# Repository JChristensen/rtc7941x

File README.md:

# MCP78411/12 RTC Break-Out Board with Temperature Sensor
https://github.com/JChristensen/rtc7941x  
README file  
Jack Christensen  
Apr-2014

## License
  
This work is licensed under the [Creative Commons Attribution-ShareAlike 4.0 International License](https://creativecommons.org/licenses/by-sa/4.0/).

## Introduction
Break-out board for the Microchip MCP78411/12 Real-Time Clock. Optionally, an MCP9800/02 temperature sensor can be installed on the board.

For an Arduino library that supports the MCP79412 RTC, see: https://github.com/JChristensen/MCP79412RTC

For an Arduino library that supports the MCP980x temperature sensor, see: https://github.com/JChristensen/MCP9800

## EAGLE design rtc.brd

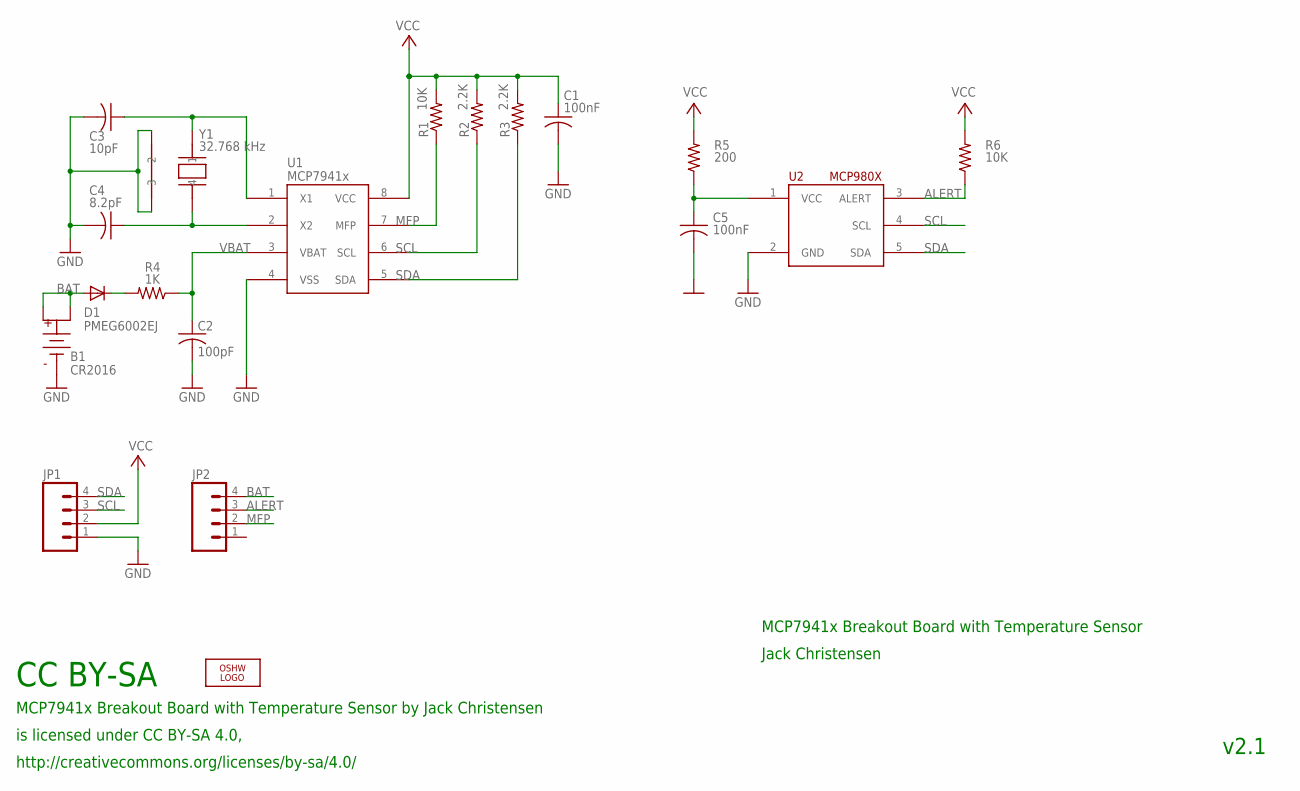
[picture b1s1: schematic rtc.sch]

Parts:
B1: CR2016; BAT-HLD-002-SMT
C1, C5: 100nF; M0805
C2: 100pF; M0805
C3: 10pF; M0805
C4: 8.2pF; M0805
D1: PMEG6002EJ; SOD-323F-A
JP1, JP2: M04LOCK; 1X04_LOCK
LOGO2: OSHW_LOGO_8MILX0150-NT; OSHW_8X150_NOTEXT
R1, R6: 10K; M0805
R2, R3: 2.2K; M0805
R4: 1K; M0805
R5: 200; M0805
U1: MCP7941x; MSOP8
U2: MCP980X; SOT23-5L
Y1: 32.768 kHz; CRYSTAL-CITIZEN-CM2XXC

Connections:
ALERT: JP2.3, R6.1, U2.3 (ALERT)
BAT: B1.POS1, B1.POS2, D1.A, JP2.4
GND: B1.NEG (B-), C1.2, C2.2, C3.2, C4.2, C5.2, JP1.1, U1.4 (VSS), U2.2 (GND), Y1.P$2 (2), Y1.P$3 (3)
MFP: JP2.2, R1.1, U1.7 (MFP)
unnamed: D1.K, R4.2
unnamed: C4.1, U1.2 (X2), Y1.P$4 (4)
unnamed: C3.1, U1.1 (X1), Y1.P$1 (1)
unnamed: C5.1, R5.1, U2.1 (VCC)
SCL: JP1.3, R2.1, U1.6 (SCL), U2.4 (SCL)
SDA: JP1.4, R3.1, U1.5 (SDA), U2.5 (SDA)
VBAT: C2.1, R4.1, U1.3 (VBAT)
VCC: C1.1, JP1.2, R1.2, R2.2, R3.2, R5.2, R6.2, U1.8 (VCC)

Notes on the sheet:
MCP7941x Breakout Board with Temperature Sensor by Jack Christensen
CC BY-SA
MCP7941x Breakout Board with Temperature Sensor
Jack Christensen
v2.1
is licensed under CC BY-SA 4.0,
http://creativecommons.org/licenses/by-sa/4.0/

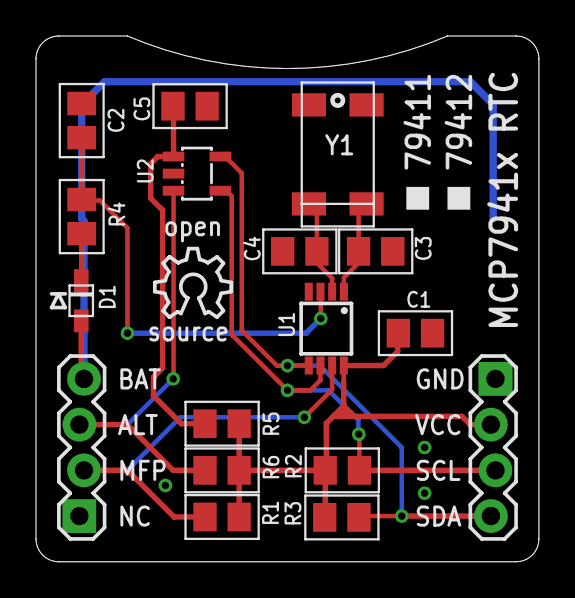
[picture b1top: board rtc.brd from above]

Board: 2 copper layers, 27.9 x 29.2 mm, 19 parts (1 on the bottom side), 12 nets.

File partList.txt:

Partlist

Exported from rtc.sch at 3/2/2019 7:11 PM

EAGLE Version 7.5.0 Copyright (c) 1988-2015 CadSoft

Assembly variant: 

Part     Value          Device                 Package                Library  Sheet

B1       CR2016         COIN-CELL-2016-SMT     BAT-HLD-002-SMT        _jc      1
C1       100nF          C-USM0805              M0805                  _jc      1
C2       100pF          C-USM0805              M0805                  _jc      1
C3       10pF           C-USM0805              M0805                  _jc      1
C4       8.2pF          C-USM0805              M0805                  _jc      1
C5       100nF          C-USM0805              M0805                  _jc      1
D1       PMEG6002EJ     DIODESOD-323F-A        SOD-323F-A             _jc      1
JP1                     M04LOCK                1X04_LOCK              SparkFun 1
JP2                     M04LOCK                1X04_LOCK              SparkFun 1
R1       10K            R-US_M0805             M0805                  _jc      1
R2       2.2K           R-US_M0805             M0805                  _jc      1
R3       2.2K           R-US_M0805             M0805                  _jc      1
R4       1K             R-US_M0805             M0805                  _jc      1
R5       200            R-US_M0805             M0805                  _jc      1
R6       10K            R-US_M0805             M0805                  _jc      1
U1       MCP7941x       MCP7941XMSOP8          MSOP8                  _jc      1
U2       MCP980X        MCP980X                SOT23-5L               _jc      1
Y1       32.768 kHz     CRYSTAL-CITIZEN-CM2XXC CRYSTAL-CITIZEN-CM2XXC _jc      1

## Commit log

2014-03-19 Initial commit. Minor routing improvements over initial batch of boards from OSH Park.
2019-03-03 v2.1
2021-12-08 Add LICENSE, README, and other misc files.
2021-12-08 Update README, image files.

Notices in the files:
parts and their libraries:
SparkFun: Licensing: CC v3.0 Share-Alike You are welcome to use this library for commercial purposes.
